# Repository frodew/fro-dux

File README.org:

* fro-dux v1

[[images/fro_dux-v1.jpeg]]

| [[images/fro_dux-v1_front.jpg]] | [[images/fro_dux-v1_back.jpg]] |

This board is a fork and customization of the [[https://github.com/andrewjrae/rae-dux][rea-dux]], which is a 36-key (diodeless!), wireless keyboard inspired by the [[https://github.com/tapioki/cephalopoda/tree/main/Architeuthis%20dux][Architeuthis Dux]].
You can find all relevant information there; this version would not exist without the others before :)

I primarily changed the routing of the tracks, being inspired by the original [[https://github.com/tapioki/cephalopoda/tree/main/Architeuthis%20dux][Architeuthis dux]] and moved the thumb-cluster more to the center.
The creator of the Architeuthis dux seems to have the awesome logo from "perce", so thank you also from my site! I could not find out who it is, maybe [[https://github.com/madebyperce/][this person]].

You can find further information in the rae-dux repo.
If you want to change something on this board, just edit 'fro_dux-v1.kicad_pcb' in KiCad and export your own gerber file.

Note, if you want to print it:

- There is only one file for both sides. Typically PCB manufacturers offer to print only more than 5 boards of one file, so the idea is to flip one board around and have the right side. I tried to make the design on both sides as similar as possible.
- If you edit the KiCAD file and export your finished version as a gerber, make sure to check "Subtract soldermask from silkscreen", so that you can solder everything together when your board arrives.
- The silkscreen currently overflows the whole keyboard as I could not find a good solution to cut the overflow. If you know how to do that, let me know :)
- I recommend following [[https://www.tzcl.me/posts/rae-dux/][this awesome guide]] to build it. Take good care to read everything before you start. But be assured: It's not that hard to do; you will be surprised.
- Check out my [[https://github.com/frodew/zmk_config][zmk-config]] for how you could configure ZMK to work on this keyboard.

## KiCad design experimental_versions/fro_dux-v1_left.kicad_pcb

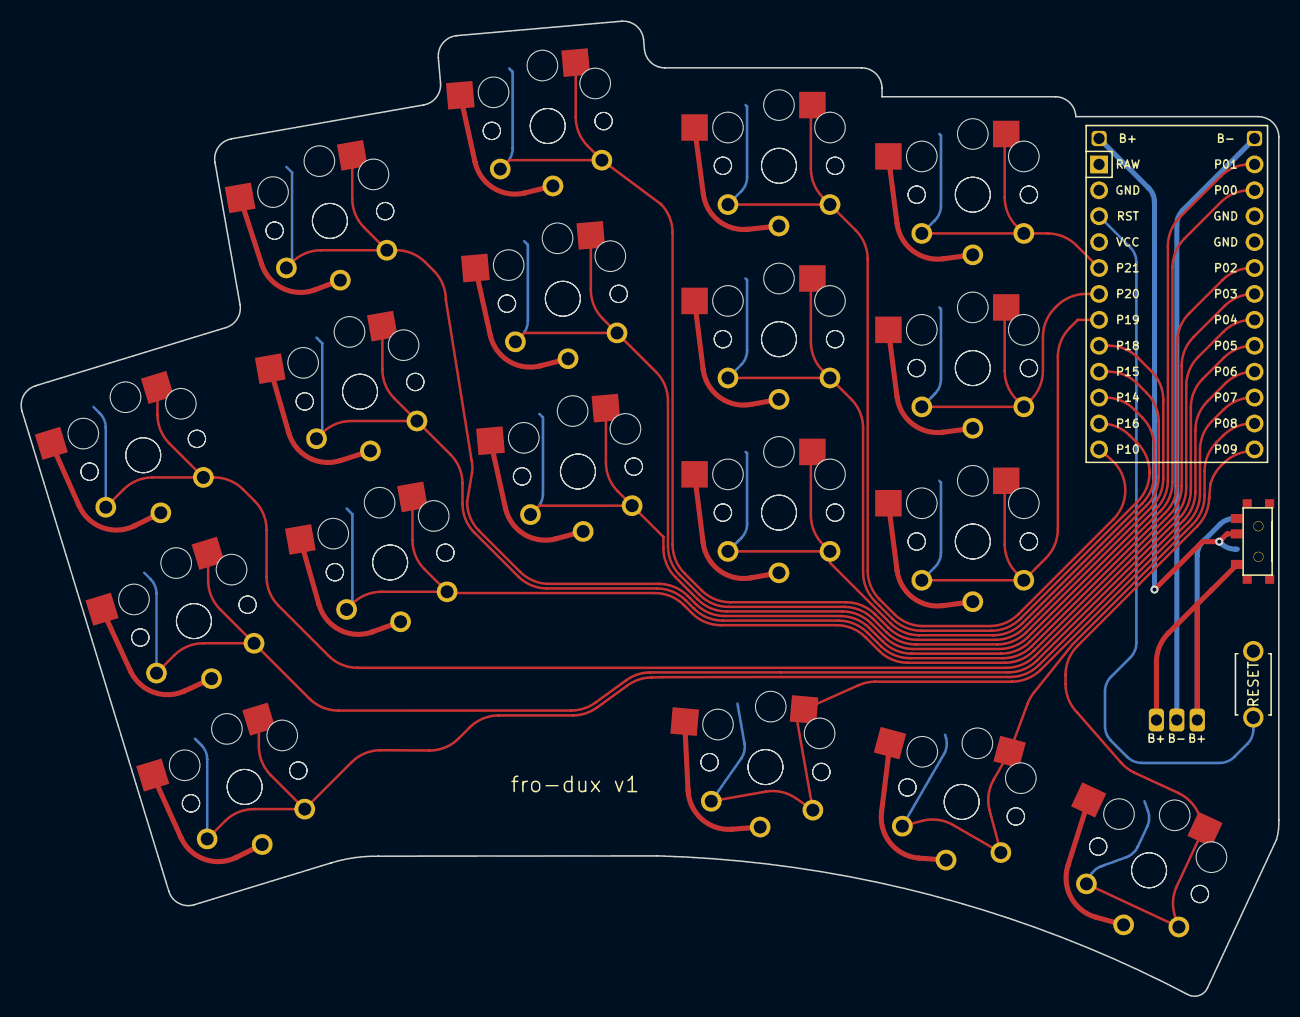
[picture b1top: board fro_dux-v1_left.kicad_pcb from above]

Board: 2 copper layers, 123.3 x 95.6 mm, 41 parts (0 on the bottom side), 23 nets.

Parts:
B1: ResetSW
MCU1: ProMicro
PAD1: bat
S1, S2, S3, S4, S5, S6, S7, S8, S9, S10, S11, S12, S13, S14, S15, S16, S17, S18, S19, S20, S21, S22, S23, S24, S25, S26, S27, S28, S29, S30, S31, S32, S33, S34, S35, S36: PG1350
T1, T2: SPDT_C128955

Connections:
Bminus: MCU1.25, PAD1.2
Bplus: MCU1.25, T1.2, T2.2
Braw: PAD1.1, T1.1, T2.1
GND: B1.2, MCU1.2, MCU1.15, MCU1.16, S1.2, S2.2, S3.2, S4.2, S5.2, S6.2, S7.2, S8.2, S9.2, S10.2, S11.2, S12.2, S13.2, S14.2, S15.2, S16.2, S17.2, S18.2, S19.2, S20.2, S21.2, S22.2, S23.2, S24.2, S25.2, S26.2, S27.2, S28.2, S29.2, S30.2, S31.2, S32.2, S33.2, S34.2, S35.2, S36.2
P0: MCU1.14, S11.1, S12.1
P1: MCU1.13, S13.1, S14.1
P2: MCU1.17, S9.1, S10.1
P3: MCU1.18, S7.1, S8.1
P4: MCU1.19, S5.1, S6.1
P5: MCU1.20, S3.1, S4.1
P6: MCU1.21, S1.1, S2.1
P7: MCU1.22, S31.1, S32.1
P8: MCU1.23, S33.1, S34.1
P9: MCU1.24, S35.1, S36.1
P10: MCU1.12, S23.1, S24.1
P14: MCU1.10, S19.1, S20.1
P15: MCU1.9, S17.1, S18.1
P16: MCU1.11, S21.1, S22.1
P18: MCU1.8, S15.1, S16.1
P19: MCU1.7, S25.1, S26.1
P20: MCU1.6, S27.1, S28.1
P21: MCU1.5, S29.1, S30.1
RST: B1.1, MCU1.3

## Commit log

2024-10-20 update repo to fro-dux v1
2025-01-30 update readme with image and zmk_config link
2025-01-30 update readme with build guide
